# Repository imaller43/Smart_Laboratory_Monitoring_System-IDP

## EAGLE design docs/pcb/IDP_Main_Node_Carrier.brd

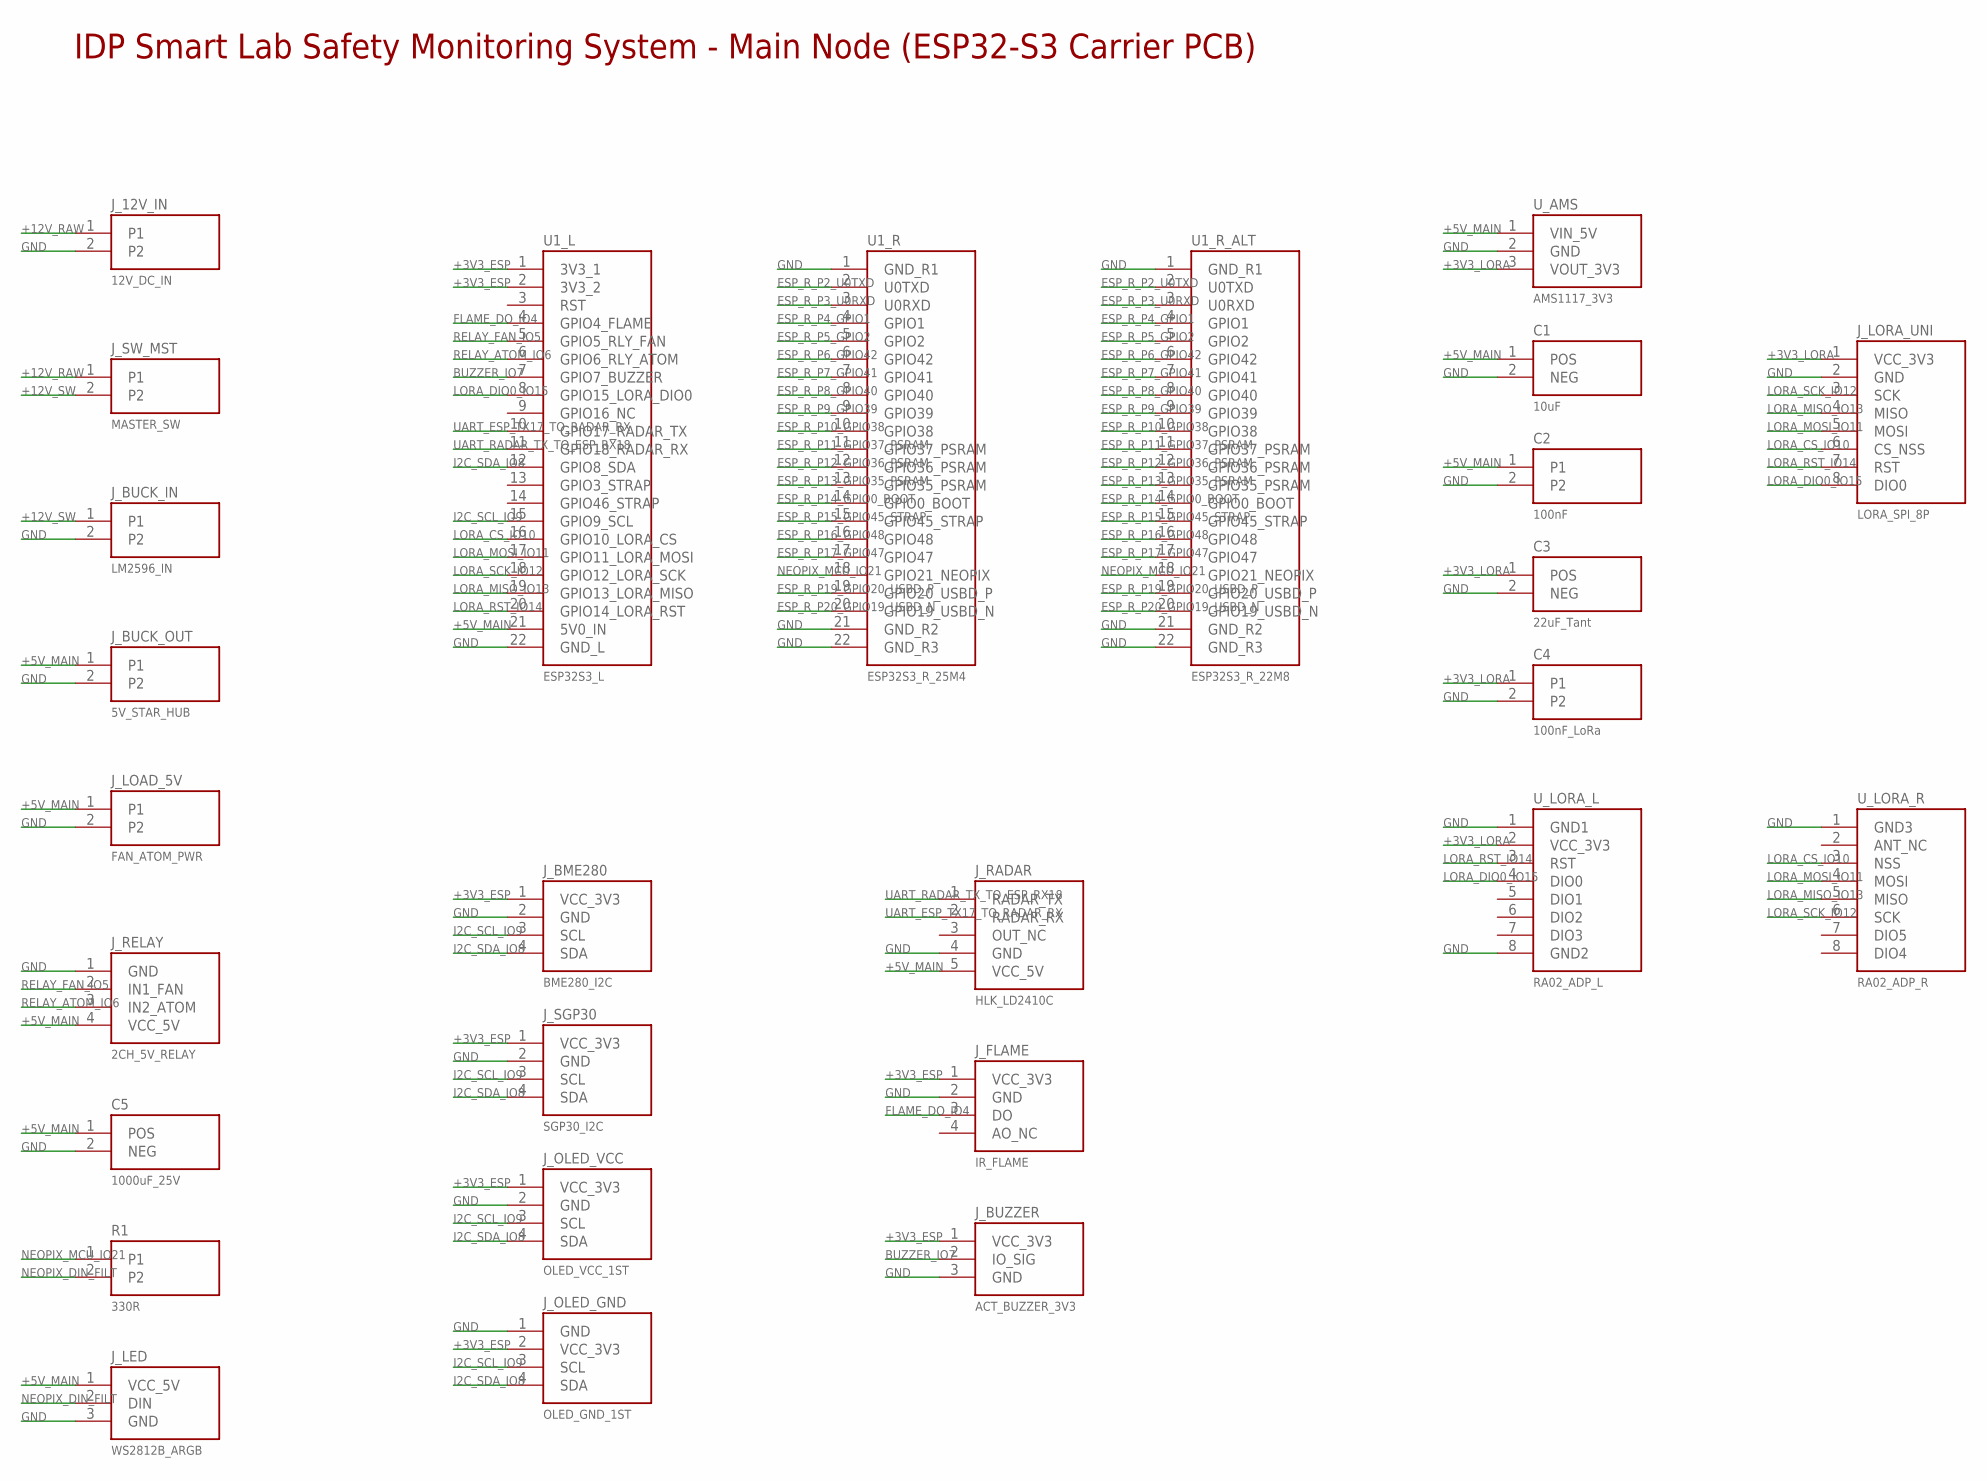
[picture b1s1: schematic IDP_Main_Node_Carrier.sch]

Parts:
C1: 10uF; CAP_RAD_5MM_P254
C2: 100nF; CAP_DISC_P254
C3: 22uF_Tant; CAP_RAD_5MM_P254
C4: 100nF_LoRa; CAP_DISC_P254
C5: 1000uF_25V; CAP_ELEC_10MM_P500
J_12V_IN: 12V_DC_IN; KF301_2P_508
J_BME280: BME280_I2C; HDR_1X4
J_BUCK_IN: LM2596_IN; KF301_2P_508
J_BUCK_OUT: 5V_STAR_HUB; KF301_2P_508
J_BUZZER: ACT_BUZZER_3V3; HDR_1X3
J_FLAME: IR_FLAME; HDR_1X4
J_LED: WS2812B_ARGB; HDR_1X3
J_LOAD_5V: FAN_ATOM_PWR; KF301_2P_508
J_LORA_UNI: LORA_SPI_8P; HDR_1X8
J_OLED_GND: OLED_GND_1ST; HDR_1X4
J_OLED_VCC: OLED_VCC_1ST; HDR_1X4
J_RADAR: HLK_LD2410C; HDR_1X5
J_RELAY: 2CH_5V_RELAY; HDR_1X4
J_SGP30: SGP30_I2C; HDR_1X4
J_SW_MST: MASTER_SW; KF301_2P_508
R1: 330R; RES_AXIAL_762
U1_L: ESP32S3_L; HDR_1X22
U1_R: ESP32S3_R_25M4; HDR_1X22
U1_R_ALT: ESP32S3_R_22M8; HDR_1X22
U_AMS: AMS1117_3V3; HDR_1X3
U_LORA_L: RA02_ADP_L; HDR_1X8
U_LORA_R: RA02_ADP_R; HDR_1X8

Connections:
+3V3_ESP: J_BME280.1 (VCC_3V3), J_BUZZER.1 (VCC_3V3), J_FLAME.1 (VCC_3V3), J_OLED_GND.2 (VCC_3V3), J_OLED_VCC.1 (VCC_3V3), J_SGP30.1 (VCC_3V3), U1_L.1 (3V3_1), U1_L.2 (3V3_2)
+3V3_LORA: C3.1 (POS), C4.1, J_LORA_UNI.1 (VCC_3V3), U_AMS.3 (VOUT_3V3), U_LORA_L.2 (VCC_3V3)
+5V_MAIN: C1.1 (POS), C2.1, C5.1 (POS), J_BUCK_OUT.1, J_LED.1 (VCC_5V), J_LOAD_5V.1, J_RADAR.5 (VCC_5V), J_RELAY.4 (VCC_5V), U1_L.21 (5V0_IN), U_AMS.1 (VIN_5V)
+12V_RAW: J_12V_IN.1, J_SW_MST.1
+12V_SW: J_BUCK_IN.1, J_SW_MST.2
BUZZER_IO7: J_BUZZER.2 (IO_SIG), U1_L.7 (GPIO7_BUZZER)
ESP_R_P2_U0TXD: U1_R.2 (U0TXD), U1_R_ALT.2 (U0TXD)
ESP_R_P3_U0RXD: U1_R.3 (U0RXD), U1_R_ALT.3 (U0RXD)
ESP_R_P4_GPIO1: U1_R.4 (GPIO1), U1_R_ALT.4 (GPIO1)
ESP_R_P5_GPIO2: U1_R.5 (GPIO2), U1_R_ALT.5 (GPIO2)
ESP_R_P6_GPIO42: U1_R.6 (GPIO42), U1_R_ALT.6 (GPIO42)
ESP_R_P7_GPIO41: U1_R.7 (GPIO41), U1_R_ALT.7 (GPIO41)
ESP_R_P8_GPIO40: U1_R.8 (GPIO40), U1_R_ALT.8 (GPIO40)
ESP_R_P9_GPIO39: U1_R.9 (GPIO39), U1_R_ALT.9 (GPIO39)
ESP_R_P10_GPIO38: U1_R.10 (GPIO38), U1_R_ALT.10 (GPIO38)
ESP_R_P11_GPIO37_PSRAM: U1_R.11 (GPIO37_PSRAM), U1_R_ALT.11 (GPIO37_PSRAM)
ESP_R_P12_GPIO36_PSRAM: U1_R.12 (GPIO36_PSRAM), U1_R_ALT.12 (GPIO36_PSRAM)
ESP_R_P13_GPIO35_PSRAM: U1_R.13 (GPIO35_PSRAM), U1_R_ALT.13 (GPIO35_PSRAM)
ESP_R_P14_GPIO0_BOOT: U1_R.14 (GPIO0_BOOT), U1_R_ALT.14 (GPIO0_BOOT)
ESP_R_P15_GPIO45_STRAP: U1_R.15 (GPIO45_STRAP), U1_R_ALT.15 (GPIO45_STRAP)
ESP_R_P16_GPIO48: U1_R.16 (GPIO48), U1_R_ALT.16 (GPIO48)
ESP_R_P17_GPIO47: U1_R.17 (GPIO47), U1_R_ALT.17 (GPIO47)
ESP_R_P19_GPIO20_USBD_P: U1_R.19 (GPIO20_USBD_P), U1_R_ALT.19 (GPIO20_USBD_P)
ESP_R_P20_GPIO19_USBD_N: U1_R.20 (GPIO19_USBD_N), U1_R_ALT.20 (GPIO19_USBD_N)
FLAME_DO_IO4: J_FLAME.3 (DO), U1_L.4 (GPIO4_FLAME)
GND: C1.2 (NEG), C2.2, C3.2 (NEG), C4.2, C5.2 (NEG), J_12V_IN.2, J_BME280.2 (GND), J_BUCK_IN.2, J_BUCK_OUT.2, J_BUZZER.3 (GND), J_FLAME.2 (GND), J_LED.3 (GND), J_LOAD_5V.2, J_LORA_UNI.2 (GND), J_OLED_GND.1 (GND), J_OLED_VCC.2 (GND), J_RADAR.4 (GND), J_RELAY.1 (GND), J_SGP30.2 (GND), U1_L.22 (GND_L), U1_R.1 (GND_R1), U1_R.21 (GND_R2), U1_R.22 (GND_R3), U1_R_ALT.1 (GND_R1), U1_R_ALT.21 (GND_R2), U1_R_ALT.22 (GND_R3), U_AMS.2 (GND), U_LORA_L.1 (GND1), U_LORA_L.8 (GND2), U_LORA_R.1 (GND3)
I2C_SCL_IO9: J_BME280.3 (SCL), J_OLED_GND.3 (SCL), J_OLED_VCC.3 (SCL), J_SGP30.3 (SCL), U1_L.15 (GPIO9_SCL)
I2C_SDA_IO8: J_BME280.4 (SDA), J_OLED_GND.4 (SDA), J_OLED_VCC.4 (SDA), J_SGP30.4 (SDA), U1_L.12 (GPIO8_SDA)
LORA_CS_IO10: J_LORA_UNI.6 (CS_NSS), U1_L.16 (GPIO10_LORA_CS), U_LORA_R.3 (NSS)
LORA_DIO0_IO15: J_LORA_UNI.8 (DIO0), U1_L.8 (GPIO15_LORA_DIO0), U_LORA_L.4 (DIO0)
LORA_MISO_IO13: J_LORA_UNI.4 (MISO), U1_L.19 (GPIO13_LORA_MISO), U_LORA_R.5 (MISO)
LORA_MOSI_IO11: J_LORA_UNI.5 (MOSI), U1_L.17 (GPIO11_LORA_MOSI), U_LORA_R.4 (MOSI)
LORA_RST_IO14: J_LORA_UNI.7 (RST), U1_L.20 (GPIO14_LORA_RST), U_LORA_L.3 (RST)
LORA_SCK_IO12: J_LORA_UNI.3 (SCK), U1_L.18 (GPIO12_LORA_SCK), U_LORA_R.6 (SCK)
NEOPIX_DIN_FILT: J_LED.2 (DIN), R1.2
NEOPIX_MCU_IO21: R1.1, U1_R.18 (GPIO21_NEOPIX), U1_R_ALT.18 (GPIO21_NEOPIX)
RELAY_ATOM_IO6: J_RELAY.3 (IN2_ATOM), U1_L.6 (GPIO6_RLY_ATOM)
RELAY_FAN_IO5: J_RELAY.2 (IN1_FAN), U1_L.5 (GPIO5_RLY_FAN)
UART_ESP_TX17_TO_RADAR_RX: J_RADAR.2 (RADAR_RX), U1_L.10 (GPIO17_RADAR_TX)
UART_RADAR_TX_TO_ESP_RX18: J_RADAR.1 (RADAR_TX), U1_L.11 (GPIO18_RADAR_RX)

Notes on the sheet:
IDP Smart Lab Safety Monitoring System - Main Node (ESP32-S3 Carrier PCB)

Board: 1 copper layer, 27 parts (0 on the bottom side), 40 nets, no tracks yet.
